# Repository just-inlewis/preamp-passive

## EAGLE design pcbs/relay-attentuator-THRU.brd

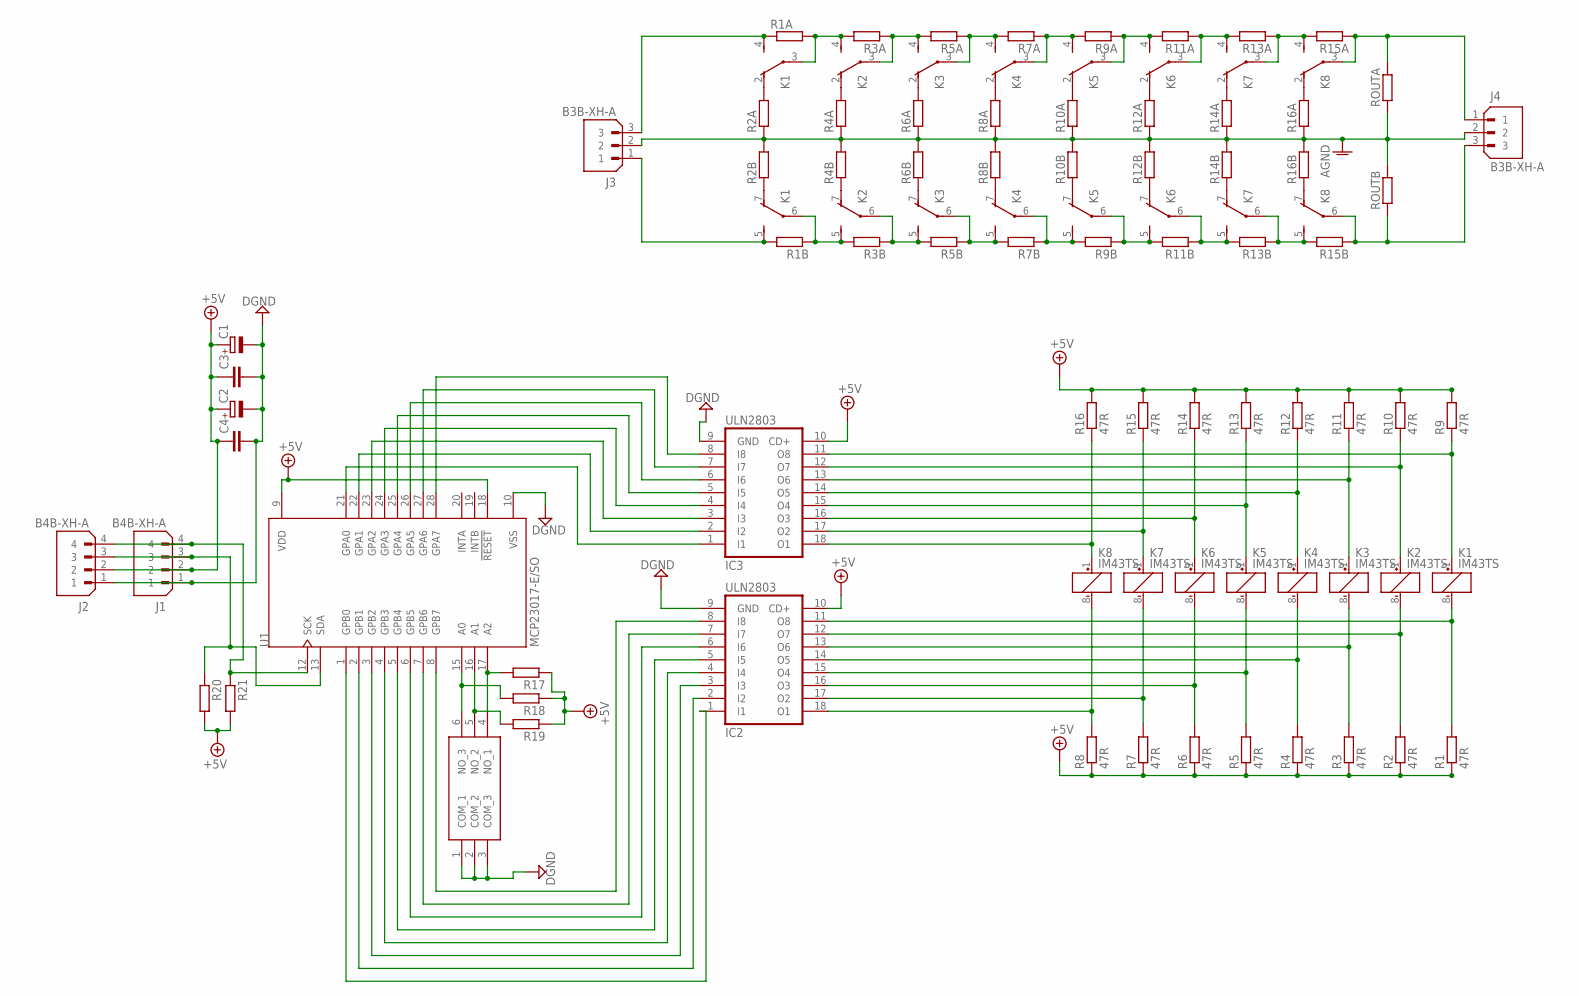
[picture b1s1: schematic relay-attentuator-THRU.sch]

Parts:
C1, C2: CPOL-EUE3.5-8; E3,5-8
C3, C4: C-EUC1206; C1206
IC2, IC3: ULN2803; SO-18W
J1, J2: B4B-XH-A; JST_B4B-XH-A
J3, J4: B3B-XH-A; JST_B3B-XH-A
K1, K2, K3, K4, K5, K6, K7, K8: IM43TS
R1, R2, R3, R4, R5, R6, R7, R8, R9, R10, R11, R12, R13, R14, R15, R16, R17, R18, R19, R20, R21: 47R; R1206
R1A, R1B, R2A, R2B, R3A, R3B, R4A, R4B, R5A, R5B, R6A, R6B, R7A, R7B, R8A, R8B, R9A, R9B, R10A, R10B, R11A, R11B, R12A, R12B, R13A, R13B, R14A, R14B, R15A, R15B, R16A, R16B: R-EU_0207/10; 0207/10
ROUTA: R-EU_0207/10; 0207/10
ROUTB: R-EU_0207/10; 0207/10
S1: 2454982-2; 24549822
U1: MCP23017-E/SO; SOIC127P1030X265-28N

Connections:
+5V: C1.+, C2.+, C3.1, C4.1, IC2.10 (CD+), IC3.10 (CD+), J1.2, J2.2, R1.1, R2.1, R3.1, R4.1, R5.1, R6.1, R7.1, R8.1, R9.2, R10.2, R11.2, R12.2, R13.2, R14.2, R15.2, R16.2, R17.1, R18.1, R19.1, R20.2, R21.2, U1.9 (VDD), U1.18 (!RESET)
AGND: J3.2, J4.2, R2A.1, R2B.2, R4A.1, R4B.2, R6A.1, R6B.2, R8A.1, R8B.2, R10A.1, R10B.2, R12A.1, R12B.2, R14A.1, R14B.2, R16A.1, R16B.2, ROUTA.1, ROUTB.2
ATT_INR: J3.1, K1.5 (S), R1B.2
DGND: C1.-, C2.-, C3.2, C4.2, IC2.9 (GND), IC3.9 (GND), J1.1, J2.1, S1.1 (COM_1), S1.2 (COM_2), S1.3 (COM_3), U1.10 (VSS)
unnamed: IC3.18 (O1), K8.1 (+), R16.1
unnamed: IC2.11 (O8), K1.8 (-), R1.2
unnamed: IC2.17 (O2), K7.8 (-), R7.2
unnamed: IC2.13 (O6), K3.8 (-), R3.2
unnamed: IC2.14 (O5), K4.8 (-), R4.2
unnamed: K2.7 (O), R4B.1
unnamed: K1.7 (O), R2B.1
unnamed: K1.2 (O), R2A.2
unnamed: IC2.18 (O1), K8.8 (-), R8.2
unnamed: IC3.17 (O2), K7.1 (+), R15.1
unnamed: IC3.16 (O3), K6.1 (+), R14.1
unnamed: IC3.15 (O4), K5.1 (+), R13.1
unnamed: IC3.14 (O5), K4.1 (+), R12.1
unnamed: IC3.13 (O6), K3.1 (+), R11.1
unnamed: IC3.12 (O7), K2.1 (+), R10.1
unnamed: IC3.11 (O8), K1.1 (+), R9.1
unnamed: K3.7 (O), R6B.1
unnamed: IC2.12 (O7), K2.8 (-), R2.2
unnamed: IC2.16 (O3), K6.8 (-), R6.2
unnamed: IC2.15 (O4), K5.8 (-), R5.2
unnamed: K4.7 (O), R8B.1
unnamed: K5.7 (O), R10B.1
unnamed: K6.7 (O), R12B.1
unnamed: K7.7 (O), R14B.1
unnamed: K8.7 (O), R16B.1
unnamed: K2.2 (O), R4A.2
unnamed: K3.2 (O), R6A.2
unnamed: K4.2 (O), R8A.2
unnamed: K5.2 (O), R10A.2
unnamed: K6.2 (O), R12A.2
unnamed: K7.2 (O), R14A.2
unnamed: K8.2 (O), R16A.2
unnamed: IC2.8 (I8), U1.8 (GPB7)
unnamed: IC2.7 (I7), U1.7 (GPB6)
unnamed: IC2.6 (I6), U1.6 (GPB5)
unnamed: IC2.5 (I5), U1.5 (GPB4)
unnamed: IC2.4 (I4), U1.4 (GPB3)
unnamed: IC2.3 (I3), U1.3 (GPB2)
unnamed: IC2.2 (I2), U1.2 (GPB1)
unnamed: IC2.1 (I1), U1.1 (GPB0)
unnamed: IC3.1 (I1), U1.21 (GPA0)
unnamed: IC3.2 (I2), U1.22 (GPA1)
unnamed: IC3.3 (I3), U1.23 (GPA2)
unnamed: IC3.4 (I4), U1.24 (GPA3)
unnamed: IC3.5 (I5), U1.25 (GPA4)
unnamed: IC3.6 (I6), U1.26 (GPA5)
unnamed: IC3.7 (I7), U1.27 (GPA6)
unnamed: IC3.8 (I8), U1.28 (GPA7)
unnamed: J3.3, K1.4 (S), R1A.1
unnamed: K7.6, K8.5 (S), R13B.1, R15B.2
unnamed: K7.3, K8.4 (S), R13A.1, R15A.2
unnamed: R18.2, S1.6 (NO_3), U1.15 (A0)
unnamed: R19.2, S1.5 (NO_2), U1.16 (A1)
unnamed: R17.2, S1.4 (NO_1), U1.17 (A2)
unnamed: J1.3, J2.3, R20.1, U1.13 (SDA)
unnamed: J1.4, J2.4, R21.1, U1.12 (SCK)
unnamed: K6.6, K7.5 (S), R11B.1, R13B.2
unnamed: J4.3, K8.6, R15B.1, ROUTB.1
unnamed: J4.1, K8.3, R15A.1, ROUTA.2
unnamed: K1.3, K2.4 (S), R1A.2, R3A.2
unnamed: K2.3, K3.4 (S), R3A.1, R5A.2
unnamed: K1.6, K2.5 (S), R1B.1, R3B.2
unnamed: K3.3, K4.4 (S), R5A.1, R7A.2
unnamed: K4.3, K5.4 (S), R7A.1, R9A.2
unnamed: K5.3, K6.4 (S), R9A.1, R11A.2
unnamed: K6.3, K7.4 (S), R11A.1, R13A.2
unnamed: K2.6, K3.5 (S), R3B.1, R5B.2
unnamed: K3.6, K4.5 (S), R5B.1, R7B.2
unnamed: K4.6, K5.5 (S), R7B.1, R9B.2
unnamed: K5.6, K6.5 (S), R9B.1, R11B.2

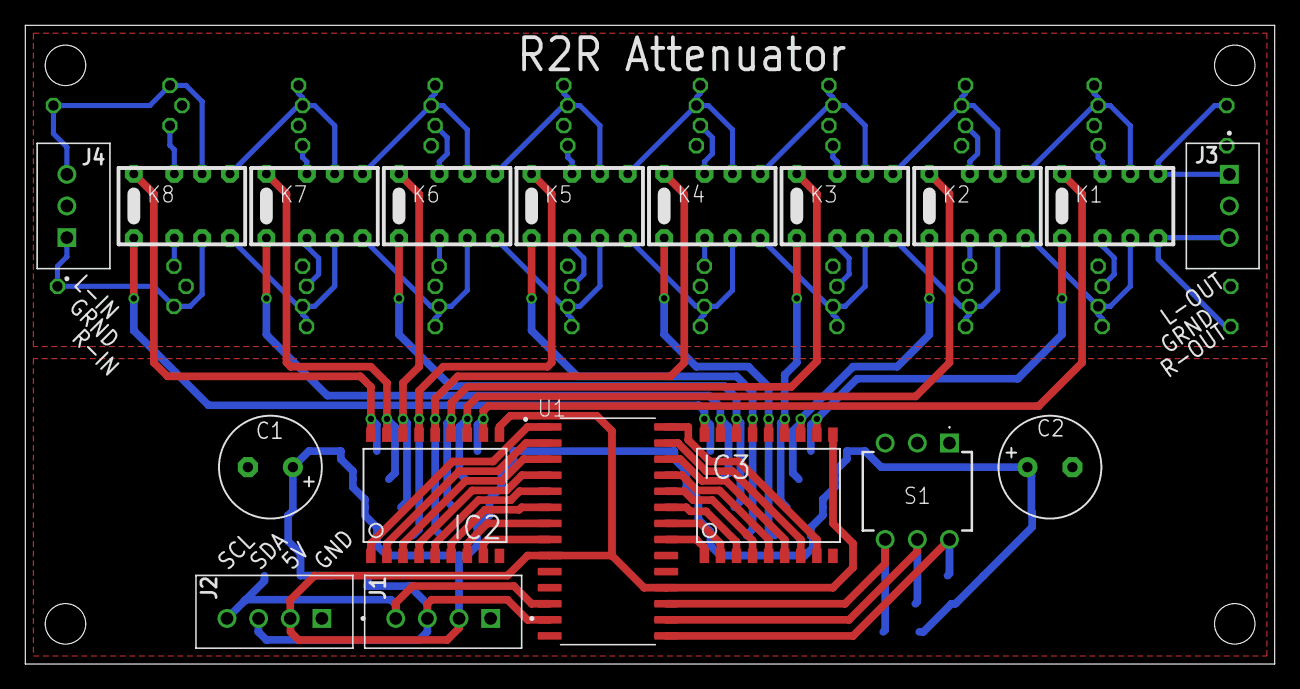
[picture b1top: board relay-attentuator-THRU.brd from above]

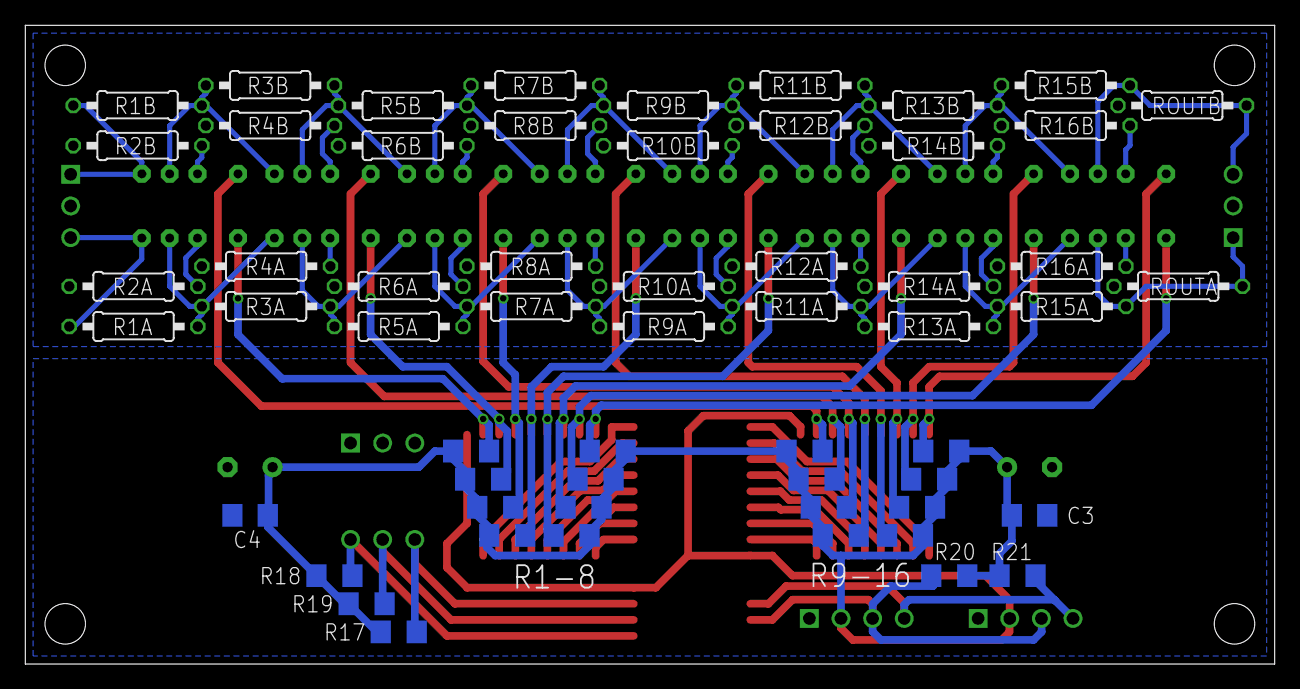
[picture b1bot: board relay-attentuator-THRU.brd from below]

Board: 2 copper layers, 98.7 x 50.5 mm, 75 parts (57 on the bottom side), 74 nets.

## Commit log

2024-11-15 new designs
2024-11-16 fixes
2024-11-24 help
